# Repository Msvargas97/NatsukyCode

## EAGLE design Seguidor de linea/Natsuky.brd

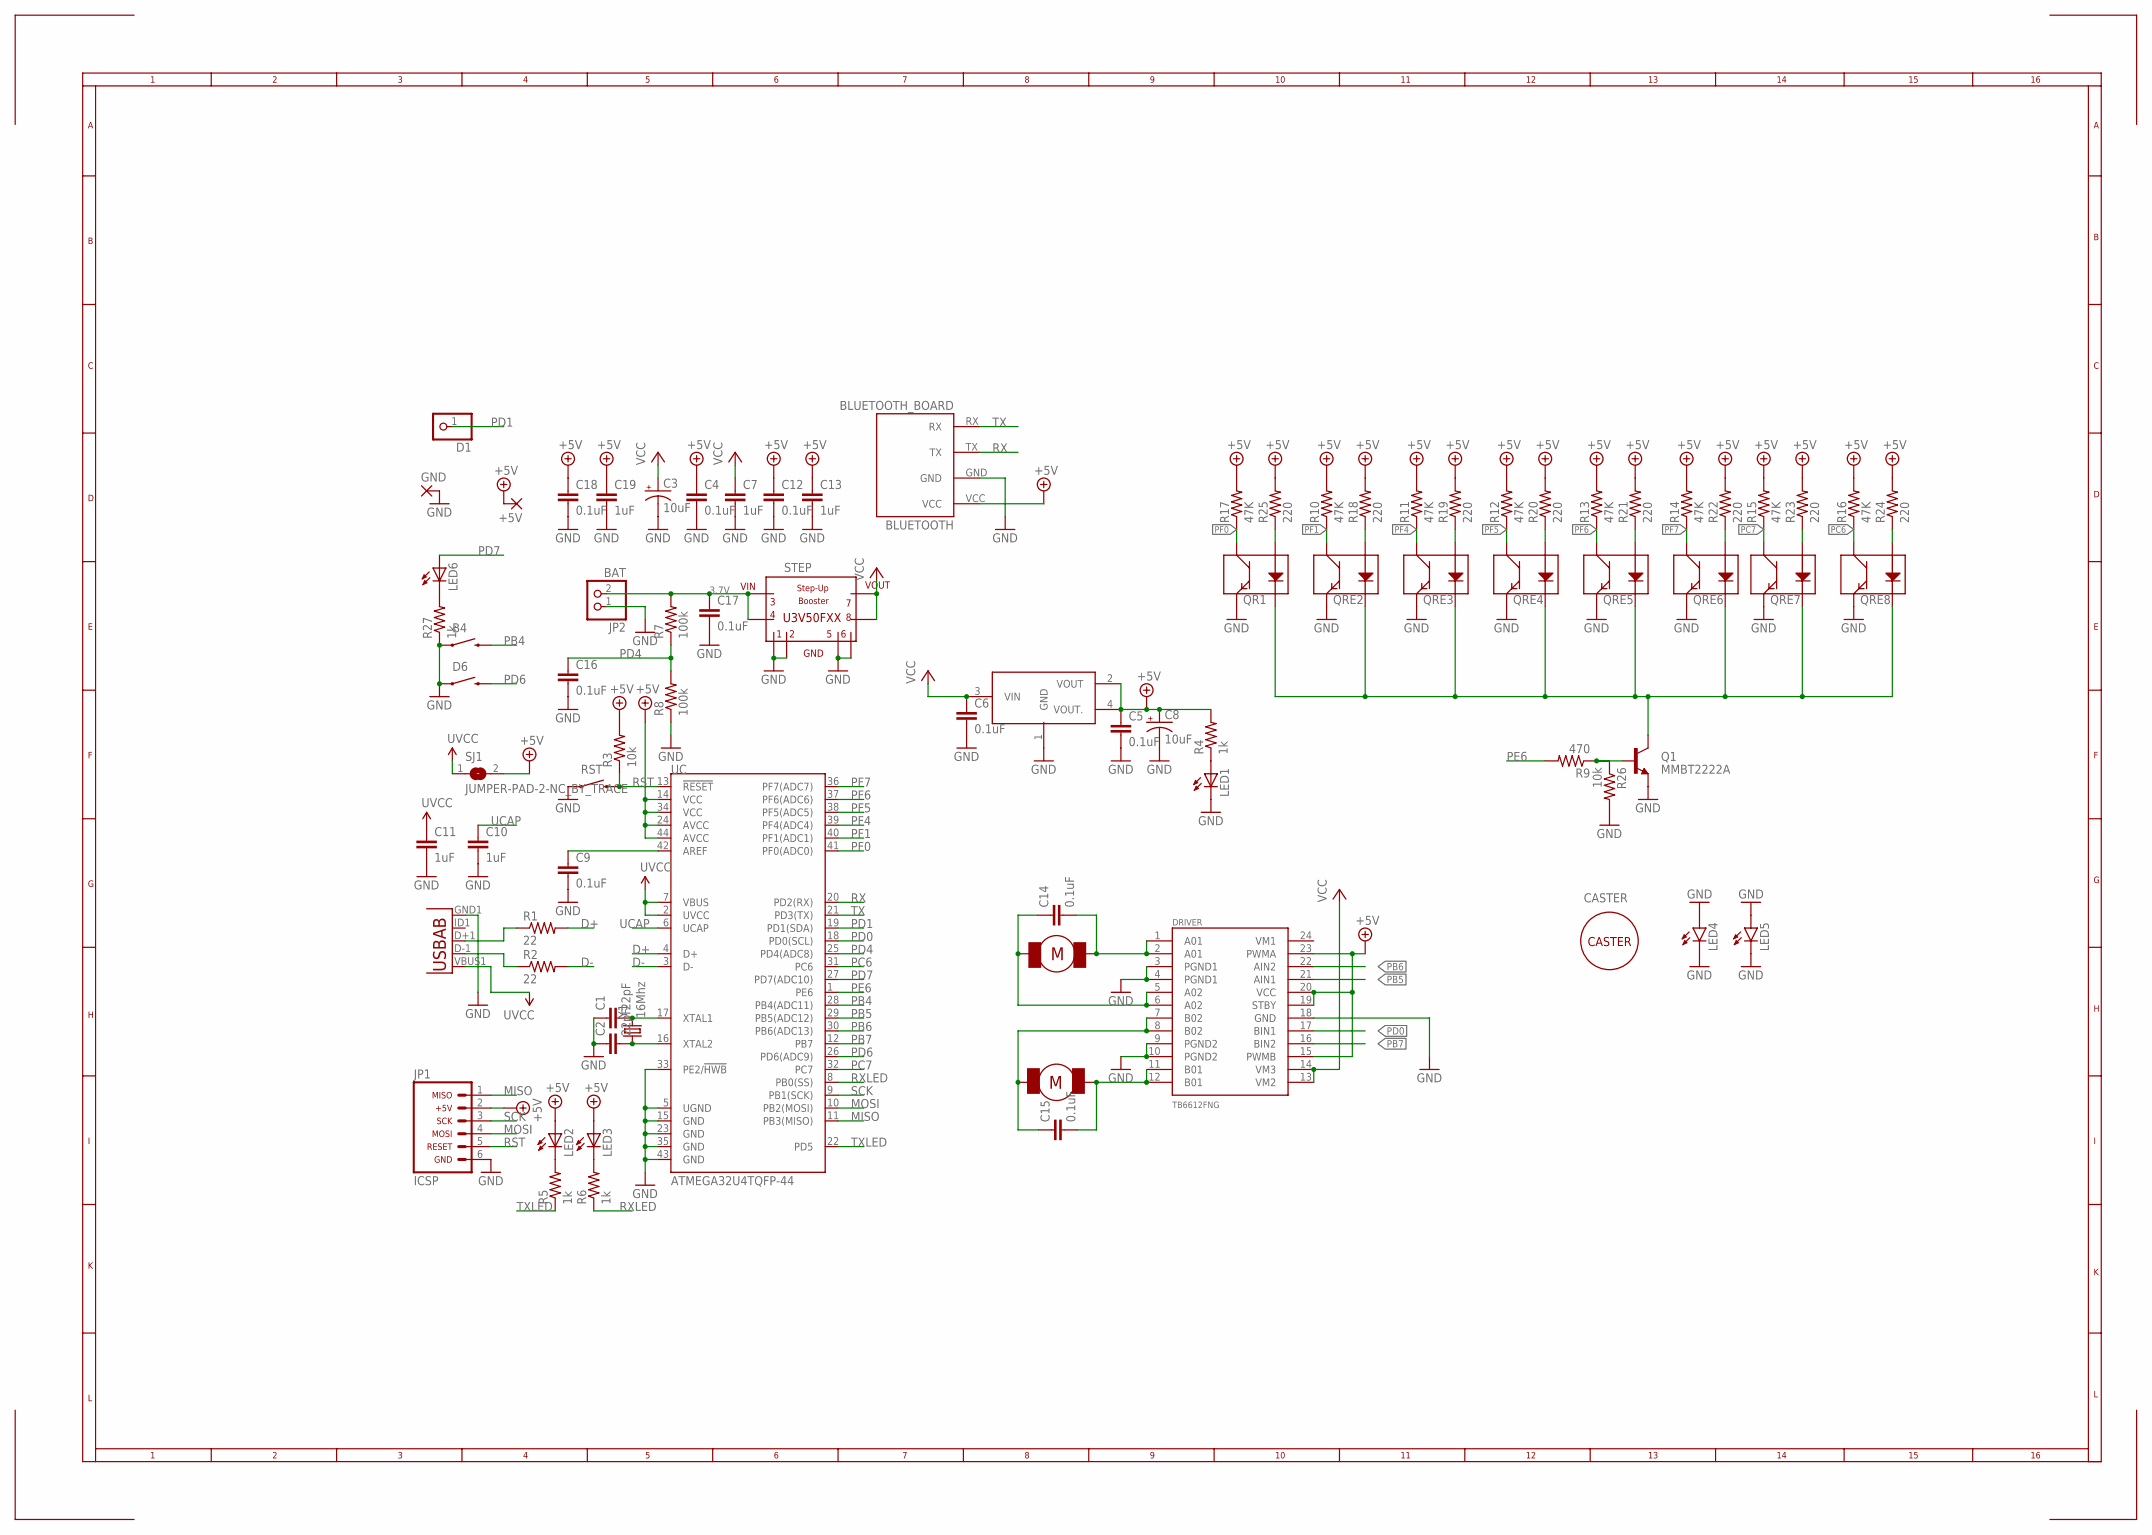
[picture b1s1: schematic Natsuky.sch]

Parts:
+5V: SMD2; SMD1,27-2,54
B4: SWITCH-MOMENTARY-2SMD-1101NE; TACTILE-SWITCH-1101NE
BLUETOOTH: BLUETOOTH_BOARD; BT_BOARD_FOOTPRINT
C1, C2: 22pF; 0805
C3: 10uF; EIA3216
C4, C5, C6, C9, C12, C14, C15, C16, C17, C18: 0.1uF; 0805
C7, C10, C11, C13, C19: 1uF; 0805
C8: 10uF; PANASONIC_D
CASTER: BALL_CASTER
D1: PINHD-1X1; 1X01
D6: SWITCH-MOMENTARY-2SMD-1101NE; TACTILE-SWITCH-1101NE
DRIVER: TB6612FNG; SSOP24
GND: SMD2; SMD1,27-2,54
JP1: ICSP; CONN-2X03
JP2: BAT; 1X02
LED1, LED2, LED3, LED6: LEDCHIPLED_1206; CHIPLED_1206
LED4, LED5: LED5MM
M1, M2: BRACKET_EXTENDED_WHITE; WHITE_EXT
Q1: MMBT2222A; SOT23-3
QR1: QRE1113SMD-W; QRE1113-W
QRE2, QRE3, QRE4, QRE5, QRE6, QRE7, QRE8: QRE1113SMD-W; QRE1113-W
R1, R2: 22; 0805
R3, R26: 10k; 0805
R4, R5, R6, R27: 1k; 0805
R7, R8: 100k; 0805
R9: 470; 0805
R10, R11, R12, R13, R14, R15, R16, R17: 47K; 0805
R18, R19, R20, R21, R22, R23, R24, R25: 220; 0805
REG: LD1117S50TR; SOT223
RST: SWITCH-MOMENTARY-2SMD-1101NE; TACTILE-SWITCH-1101NE
SJ1: JUMPER-PAD-2-NC_BY_TRACE; SJ
STEP: STEP-UP; U3V50F12
UC: ATMEGA32U4TQFP-44; TQFP44
X1: usb; USB-AB-MICRO-SMD-V03-IN&OUT
Y1: 16Mhz; HC49US

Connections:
3.3V: C11.1, SJ1.1, UC.2 (UVCC), UC.7 (VBUS), X1.VBUS1 (VBUS)
3.7V: C17.1, JP2.2, R7.2, STEP.VIN, STEP.VIN_4 (VIN4)
+5V: +5V.1, BLUETOOTH.VCC, C4.1, C5.1, C8.+, C12.1, C13.1, C18.1, C19.1, DRIVER.15 (PWMB), DRIVER.19 (STBY), DRIVER.20 (VCC), DRIVER.23 (PWMA), JP1.2, LED2.A, LED3.A, R3.2, R4.2, R10.2, R11.2, R12.2, R13.2, R14.2, R15.2, R16.2, R17.2, R18.2, R19.2, R20.2, R21.2, R22.2, R23.2, R24.2, R25.2, REG.2 (VOUT), REG.4 (VOUT.), SJ1.2, UC.14 (VCC), UC.24 (AVCC), UC.34 (VCC), UC.44 (AVCC)
COLECTOR_EMISORES: Q1.3 (C), QR1.2 (K), QRE2.2 (K), QRE3.2 (K), QRE4.2 (K), QRE5.2 (K), QRE6.2 (K), QRE7.2 (K), QRE8.2 (K)
D+: R1.2, UC.4 (D+)
D-: R2.2, UC.3 (D-)
GND: B4.1, BLUETOOTH.GND, C1.1, C2.1, C3.C (-), C4.2, C5.2, C6.2, C7.2, C8.-, C9.2, C10.2, C11.2, C12.2, C13.2, C16.2, C17.2, C18.2, C19.2, D6.1, DRIVER.3 (PGND1), DRIVER.4 (PGND1), DRIVER.9 (PGND2), DRIVER.10 (PGND2), DRIVER.18 (GND), GND.1, JP1.6, JP2.1, LED1.C, LED4.A, LED4.K (C), LED5.A, LED5.K (C), Q1.2 (E), QR1.4 (E), QRE2.4 (E), QRE3.4 (E), QRE4.4 (E), QRE5.4 (E), QRE6.4 (E), QRE7.4 (E), QRE8.4 (E), R8.1, R26.2, R27.1, REG.1 (GND), RST.1, STEP.GND_OUT (GND_VOUT), STEP.GND_OUT_1 (GND_OUT1), STEP.GND_VIN, STEP.GND_VIN_1 (GND_VIN1), UC.5 (UGND), UC.15 (GND), UC.23 (GND), UC.33 (PE2/!HWB), UC.35 (GND), UC.43 (GND), X1.GND1 (GND)
M1: C14.2, DRIVER.1 (A01), DRIVER.2 (A01), M2.M1
M2: C14.1, DRIVER.5 (A02), DRIVER.6 (A02), M2.M2
M3: C15.1, DRIVER.7 (B02), DRIVER.8 (B02), M1.M1
M4: C15.2, DRIVER.11 (B01), DRIVER.12 (B01), M1.M2
MISO: JP1.1, UC.11 (PB3(MISO))
MOSI: JP1.4, UC.10 (PB2(MOSI))
unnamed: C1.2, UC.17 (XTAL1), Y1.2
unnamed: C2.2, UC.16 (XTAL2), Y1.1
unnamed: Q1.1 (B), R9.1, R26.1
unnamed: LED1.A, R4.1
unnamed: LED2.C, R5.2
unnamed: LED3.C, R6.2
unnamed: R2.1, X1.D-1 (D-)
unnamed: R1.1, X1.D+1 (D+)
unnamed: C9.1, UC.42 (AREF)
unnamed: LED6.C, R27.2
unnamed: QRE2.1 (A), R18.1
unnamed: QRE3.1 (A), R19.1
unnamed: QRE4.1 (A), R20.1
unnamed: QRE5.1 (A), R21.1
unnamed: QRE6.1 (A), R22.1
unnamed: QRE7.1 (A), R23.1
unnamed: QRE8.1 (A), R24.1
unnamed: QR1.1 (A), R25.1
PB4: B4.2, UC.28 (PB4(ADC11))
PB5: DRIVER.21 (AIN1), UC.29 (PB5(ADC12))
PB6: DRIVER.22 (AIN2), UC.30 (PB6(ADC13))
PB7: DRIVER.16 (BIN2), UC.12 (PB7)
PC6: QRE8.3 (C), R16.1, UC.31 (PC6)
PC7: QRE7.3 (C), R15.1, UC.32 (PC7)
PD0: DRIVER.17 (BIN1), UC.18 (PD0(SCL))
PD1: D1.1, UC.19 (PD1(SDA))
PD4: C16.1, R7.1, R8.2, UC.25 (PD4(ADC8))
PD6: D6.2, UC.26 (PD6(ADC9))
PD7: LED6.A, UC.27 (PD7(ADC10))
PE6: R9.2, UC.1 (PE6)
PF0: QR1.3 (C), R17.1, UC.41 (PF0(ADC0))
PF1: QRE2.3 (C), R10.1, UC.40 (PF1(ADC1))
PF4: QRE3.3 (C), R11.1, UC.39 (PF4(ADC4))
PF5: QRE4.3 (C), R12.1, UC.38 (PF5(ADC5))
PF6: QRE5.3 (C), R13.1, UC.37 (PF6(ADC6))
PF7: QRE6.3 (C), R14.1, UC.36 (PF7(ADC7))
RST: JP1.5, R3.1, RST.2, UC.13 (!RESET)
RX: BLUETOOTH.TX, UC.20 (PD2(RX))
RXLED: R6.1, UC.8 (PB0(SS))
SCK: JP1.3, UC.9 (PB1(SCK))
TX: BLUETOOTH.RX, UC.21 (PD3(TX))
TXLED: R5.1, UC.22 (PD5)
UCAP: C10.1, UC.6 (UCAP)
VCC: C3.A (+), C6.1, C7.1, DRIVER.13 (VM2), DRIVER.14 (VM3), REG.3 (VIN), STEP.VOUT, STEP.VOUT_4 (VOUT4)

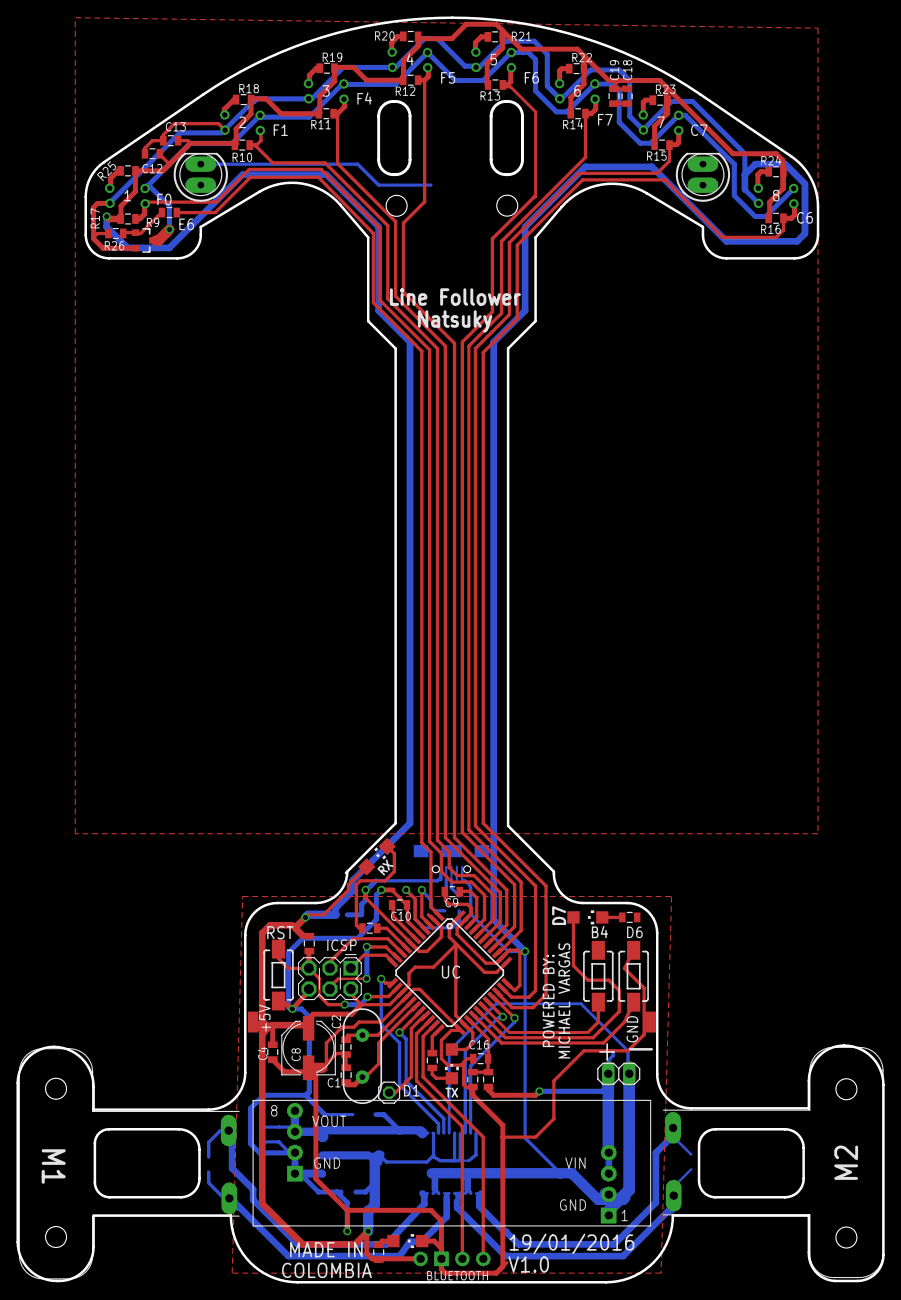
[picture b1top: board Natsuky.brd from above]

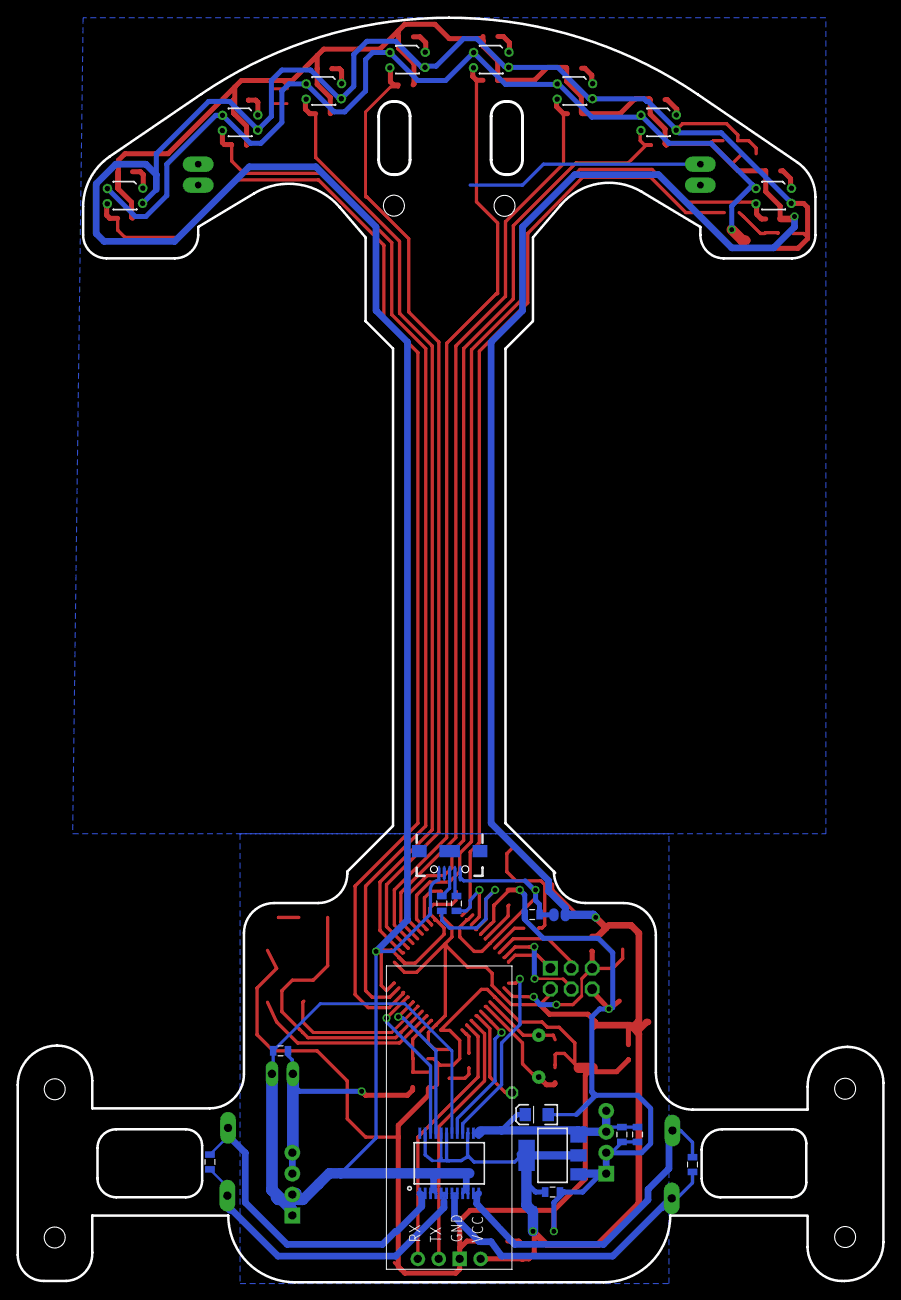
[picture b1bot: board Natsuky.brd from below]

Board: 2 copper layers, 105.0 x 153.5 mm, 80 parts (23 on the bottom side), 57 nets.

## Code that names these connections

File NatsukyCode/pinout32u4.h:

/* 
* pinout32u4.h
*
* Created: 12/02/2016 4:37:34 p. m.
* Author: Michael Vargas
*/
#ifndef pinout32u4_h__
#define pinout32u4_h__

#if defined(__AVR_ATmega32U4__) || defined (__AVR_ATmega16u4__)

#include <avr/io.h>

//#define min(a,b) ((a)<(b)?(a):(b))
// #define max(a,b) ((a)>(b)?(a):(b))
#define constrain(amt,low,high) ((amt)<(low)?(low):((amt)>(high)?(high):(amt)))
#define round(x)     ((x)>=0?(long)((x)+0.5):(long)((x)-0.5))
#define lowByte(w) ((uint8_t) ((w) & 0xff))
#define highByte(w) ((uint8_t) ((w) >> 8))
#define bitRead(value, bit) (((value) >> (bit)) & 0x01)
#define bitSet(value, bit) ((value) |= (1UL << (bit)))
#define bitClear(value, bit) ((value) &= ~(1UL << (bit)))
#define bitWrite(value, bit, bitvalue) (bitvalue ? bitSet(value, bit) : bitClear(value, bit))
#define CANTIDAD_ELEMENTOS(x) (sizeof (x) / sizeof (*(x)))

#define INPUT 				0
#define OUTPUT				1
#define LOW					0
#define HIGH				1
#define TOGGLE				0xFF
#define HIGH_IMPEDANCE		0
#define PULL_UP_ENABLED		1


//Puerto B
#define IO_PB0			0
#define IO_PB1			1
#define IO_PB2			2
#define IO_PB3			3
#define IO_PB4			4
#define IO_PB5			5
#define IO_PB6			6
#define IO_PB7			7
//Puerto D
#define IO_PD0			8
#define IO_PD1			9
#define IO_PD2			10
#define IO_PD3			11
#define IO_PD4			12
#define IO_PD5			13
#define IO_PD6			14
#define IO_PD7			15
//Puerto F
#define IO_PF0			16
#define IO_PF1			17
#define IO_PF4			18
#define IO_PF5			19
#define IO_PF6			20
#define IO_PF7			21
//Puerto C
#define IO_PC6			22
#define IO_PC7			23
//Puerto E
#define IO_PE6			24

//Define salidas PWM
#define PWM0A 0
#define PWM0B 1
#define PWM1A 2
#define PWM1B 3
#define PWM1C 4
#define PWM3A 5
//#define PWM3B 6
//#define PWM3C 7

//Estructura y clase creada gracias a libreria de Pololu
struct IOStruct
{
	// if these aren't volatile, the compiler sometimes incorrectly optimizes away operations involving these registers:
	volatile unsigned char* pinRegister;
	volatile unsigned char* portRegister;
	volatile unsigned char* ddrRegister;
	unsigned char bitmask;
};


#ifdef __cplusplus

class Analog {
	public:
	Analog();
	inline static void init(){
	ADCSRA = 0;
	ADMUX = 0;
	ADCSRB = 0;
	ADCSRA |= (1 << ADPS2) | (1 << ADPS1); // prescalar = 64
	ADMUX |= (1 << REFS0); // reference voltage from internal source
	ADCSRA |= (1 << ADEN); // enable ADC
	DIDR0 |= ((1<<ADC5D) | (1<<ADC6D) | (1<<ADC7D) | (1<<ADC4D)); //Deshabilita la funcion digital de los pines analogos
	//Deshabilitar JTAG para usar el puerto F. (Si no deshabilita el ADC no lee valores por debajo de 200)
	MCUCR |= (1<<JTD);
	MCUCR |= (1<<JTD);
	ADCSRA |= (1<<ADHSM);
	ADCSRB = 0;
	ADCSRA |= (1 << ADSC); // start A2D conversions
	}
    inline static uint16_t read(unsigned char ch)
    {
	    if (ch >=8)//
	    {
		    ch -= 0x08;//ch - 8
		    ADCSRB |=  (1 << MUX5);
	    }
	    else
	    {
		    ADCSRB &=  ~(1 << MUX5);   // Limpia el bit para canales mayores a 7
	    }
// 	    prevChannel = ADMUX; //Limpia el canal anterior y guarda la configuracion de voltaje de referencia
// 	    prevChannel &= 0b11100000;
	    ADMUX = 0b01000000;
	    ADMUX |= ch; // selecting channel
	    ADCSRA |= ((1<<ADSC) | (1<<ADEN));   // Inicia la conversion
	    while(!(ADCSRA & (1<<ADIF))); //Espera que se complete la conversion
	    ADCSRA &= (~(1<<ADEN));
	    return (ADC);
    }

};
class Digital
{
	public:

	// constructor (doesn't do anything)
	Digital();

	// gets a structure with pointers to the three digital I/O registers associated
	// with the specified pin (DDR, PORT, and PIN) along with a bitmask with a
	// 1 in the position of the specified pin and 0s everywhere else.
	inline static void getIORegisters(struct IOStruct* io, unsigned char pin)
	{
		io->pinRegister = 0;
		io->portRegister = 0;
		io->ddrRegister = 0;
		io->bitmask = 0;
		
		if (pin < 8)			// pin 0 = PB0, ..., 7 = PB7
		{
			io->pinRegister = (unsigned char*)&PINB;
			io->portRegister = (unsigned char*)&PORTB;
			io->ddrRegister = (unsigned char*)&DDRB;
			io->bitmask = 1 << pin;
		}
		else if (pin < 16)
		{
			io->pinRegister = (unsigned char*)&PIND;
			io->portRegister = (unsigned char*)&PORTD;
			io->ddrRegister = (unsigned char*)&DDRD;
			io->bitmask = 1 << (pin - 8);
		}
		else if (pin < 22)		// Puerto F
		{
			io->pinRegister = (unsigned char*)&PINF;
			io->portRegister = (unsigned char*)&PORTF;
			io->ddrRegister = (unsigned char*)&DDRF;
			io->bitmask = 1 << ((pin - 16) > 1 ? (pin-14) : (pin - 16));
			}else if (pin < 24){
			io->pinRegister = (unsigned char*)&PINC;
			io->portRegister = (unsigned char*)&PORTC;
			io->ddrRegister = (unsigned char*)&DDRC;
			io->bitmask = 1 << (pin-16);
			}else if (pin==24){
			io->pinRegister = (unsigned char*)&PINE;
			io->portRegister = (unsigned char*)&PORTE;
			io->ddrRegister = (unsigned char*)&DDRE;
			io->bitmask = 1 << 6;
		}
		
	}


	// low-level method for setting the data direction (i.e. input or output) of an pin or set of pins
	// described by an IOStruct pointer.
	inline static void setDataDirection(struct IOStruct* ioPin, unsigned char val)
	{
		if (val)
		*(ioPin->ddrRegister) |= ioPin->bitmask;
		else
		*(ioPin->ddrRegister) &= ~ioPin->bitmask;
	}


	// low-level method for setting the PORT register value of an pin or set of pins
	// described by an IOStruct pointer.  If the pin is an input, this lets you choose between
	// setting it as high-impedance (val = 0) or enabling the internal pull-up (val = 1).  If the pin is an
	// output, this lets you choose between driving low (val = 0) and driving high (val = 1).
	// NOTE: if val is 0xFF (255), this method will toggle the PORT register pin(s).
	inline static void setOutputValue(struct IOStruct* ioPin, unsigned char val)
	{
		if (val == 0xFF)
		*(ioPin->portRegister) ^= ioPin->bitmask;
		else if (val)
		*(ioPin->portRegister) |= ioPin->bitmask;
		else
		*(ioPin->portRegister) &= ~ioPin->bitmask;
	}


	// low-level method for reading the value of the PIN register for an pin or set of pins
	// described by an IOStruct pointer.
	inline static bool getInputValue(struct IOStruct* ioPin)
	{
		return *(ioPin->pinRegister) & ioPin->bitmask;
	}


	// high-level method for setting the specified pin as an output with the specified output state.
	// An outputState value of 0 will cause the pin to drive low; a value of 1 will cause the pin to
	// drive high.  A value of 0xFF (255) will toggle the output state of the pin (i.e. high -> low and
	// low -> high).
	inline static void setOutput(unsigned char pin, unsigned char outputState)
	{
		struct IOStruct registers;
		getIORegisters(&registers, pin);
		setOutputValue(&registers, outputState);
		setDataDirection(&registers, 1);
	}


	// high-level method for setting the specified pin as an input with the specified input state.
	// An inputState value of 0 will cause the pin to be a high-impedance input; a value of 1 will enable the
	// pin's internal pull-up resistor, which weakly pulls it to Vcc.  A value of 0xFF (255) will toggle the
	// input state.
	inline static void setInput(unsigned char pin, unsigned char inputState)
	{
		struct IOStruct registers;
		getIORegisters(&registers, pin);
		setDataDirection(&registers, 0);
		setOutputValue(&registers, inputState);
	}


	// high-level method for reading the input value of the specified pin.  If the voltage on the pin is low,
	// this method will return 0.  Otherwise, it will return a non-zero result that depends on the value of
	// the pin.
	inline static unsigned char isInputHigh(unsigned char pin)
	{
		struct IOStruct registers;
		getIORegisters(&registers, pin);
		return getInputValue(&registers);
	}

};

extern "C"{
		inline static long map(long x, long in_min, long in_Max, long out_min, long out_Max)
		{
			return(x - in_min) * (out_Max - out_min) / (in_Max - in_min) + out_min;
		}
		
 enum prescalerTimer
	{ PRESCALER_1=1 , PRESCALER_8 = 2 , PRESCALER_64 = 3, PRESCALER_256=4, PRESCALER_1024=5};

#endif
};

#endif
#endif //__PINOUT32U4_H__

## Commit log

2016-02-22 :confetti_ball: Added .gitattributes & .gitignore files
2016-02-22 Version inicial Seguidor de linea ATmel
    Version basica del codigo usando librerias propias, para el control del
    seguidor de linea.
    -Caracteristicas:
    sensores IR
    motores 10:1
    encoders opticos
2016-03-30 Añadido control BT
    Nuevo código base, comunicacion bluetooth

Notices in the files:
parts and their libraries:
SparkFun-Capacitors: Licensing: Creative Commons ShareAlike 4.0 International - https://creativecommons.org/licenses/by-sa/4.0
